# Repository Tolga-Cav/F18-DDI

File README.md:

# F18-DDI
Standalone F18 DDI with a screen to serve as general purpose second display for DCS

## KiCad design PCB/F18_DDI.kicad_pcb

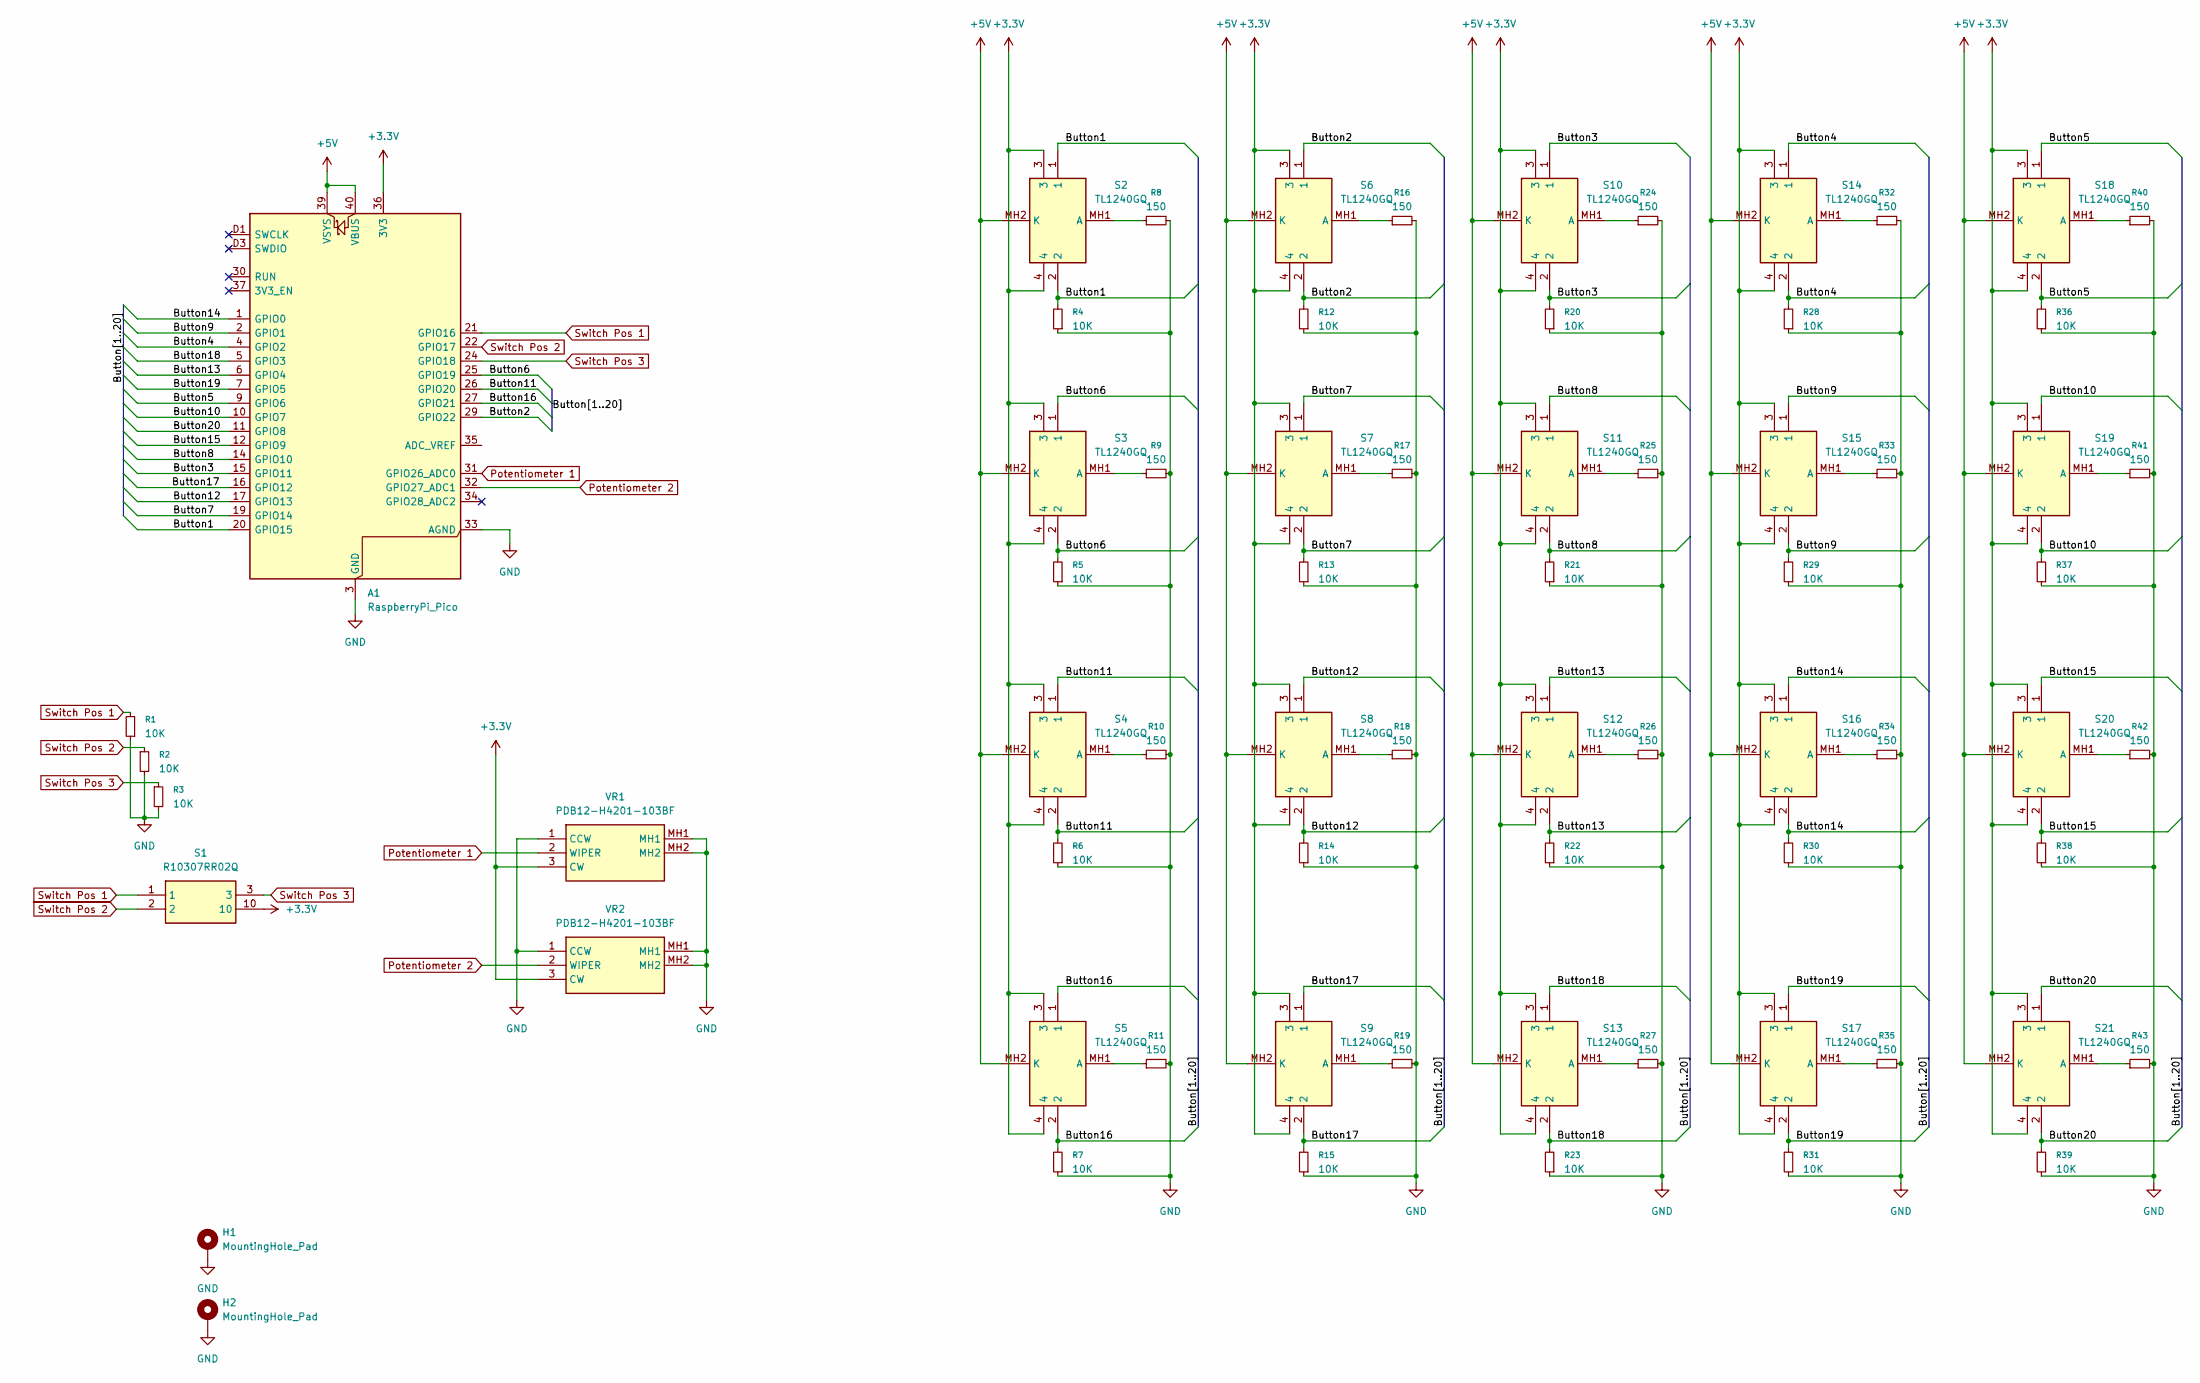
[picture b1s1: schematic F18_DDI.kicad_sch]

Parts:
A1: RaspberryPi_Pico; RaspberryPi_Pico_Common_Unspecified
H1, H2: MountingHole_Pad; MountingHole_3.2mm_M3_DIN965_Pad
R1, R2, R3, R4, R5, R6, R7, R12, R13, R14, R15, R20, R21, R22, R23, R28, R29, R30, R31, R36, R37, R38, R39: 10K; R_1206_3216Metric_Pad1.30x1.75mm_HandSolder
R8, R9, R10, R11, R16, R17, R18, R19, R24, R25, R26, R27, R32, R33, R34, R35, R40, R41, R42, R43: 150; R_1206_3216Metric_Pad1.30x1.75mm_HandSolder
S1: R10307RR02Q; R10305RN02Q; Mouser Part Number 611-R10307RR02Q
S2, S3, S4, S5, S6, S7, S8, S9, S10, S11, S12, S13, S14, S15, S16, S17, S18, S19, S20, S21: TL1240GQ; Mouser Part Number 612-TL1240GQ
VR1, VR2: PDB12-H4201-103BF; PDB12H4201103BF; Mouser Part Number 652-PDB12-H4201103BF

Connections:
+3.3V: A1.36 (3V3), S1.10, S2.3, S2.4, S3.3, S3.4, S4.3, S4.4, S5.3, S5.4, S6.3, S6.4, S7.3, S7.4, S8.3, S8.4, S9.3, S9.4, S10.3, S10.4, S11.3, S11.4, S12.3, S12.4, S13.3, S13.4, S14.3, S14.4, S15.3, S15.4, S16.3, S16.4, S17.3, S17.4, S18.3, S18.4, S19.3, S19.4, S20.3, S20.4, S21.3, S21.4, VR1.3 (CW), VR2.3 (CW)
+5V: A1.39 (VSYS), A1.40 (VBUS), S2.MH2 (K), S3.MH2 (K), S4.MH2 (K), S5.MH2 (K), S6.MH2 (K), S7.MH2 (K), S8.MH2 (K), S9.MH2 (K), S10.MH2 (K), S11.MH2 (K), S12.MH2 (K), S13.MH2 (K), S14.MH2 (K), S15.MH2 (K), S16.MH2 (K), S17.MH2 (K), S18.MH2 (K), S19.MH2 (K), S20.MH2 (K), S21.MH2 (K)
/Button1: A1.20 (GPIO15), R4.2, S2.1, S2.2
/Button2: A1.29 (GPIO22), R12.2, S6.1, S6.2
/Button3: A1.15 (GPIO11), R20.2, S10.1, S10.2
/Button4: A1.4 (GPIO2), R28.2, S14.1, S14.2
/Button5: A1.9 (GPIO6), R36.2, S18.1, S18.2
/Button6: A1.25 (GPIO19), R5.2, S3.1, S3.2
/Button7: A1.19 (GPIO14), R13.2, S7.1, S7.2
/Button8: A1.14 (GPIO10), R21.2, S11.1, S11.2
/Button9: A1.2 (GPIO1), R29.2, S15.1, S15.2
/Button10: A1.10 (GPIO7), R37.2, S19.1, S19.2
/Button11: A1.26 (GPIO20), R6.2, S4.1, S4.2
/Button12: A1.17 (GPIO13), R14.2, S8.1, S8.2
/Button13: A1.6 (GPIO4), R22.2, S12.1, S12.2
/Button14: A1.1 (GPIO0), R30.2, S16.1, S16.2
/Button15: A1.12 (GPIO9), R38.2, S20.1, S20.2
/Button16: A1.27 (GPIO21), R7.2, S5.1, S5.2
/Button17: A1.16 (GPIO12), R15.2, S9.1, S9.2
/Button18: A1.5 (GPIO3), R23.2, S13.1, S13.2
/Button19: A1.7 (GPIO5), R31.2, S17.1, S17.2
/Button20: A1.11 (GPIO8), R39.2, S21.1, S21.2
GND: A1.3 (GND), A1.8 (GND), A1.13 (GND), A1.18 (GND), A1.23 (GND), A1.28 (GND), A1.33 (AGND), A1.38 (GND), A1.D2 (GND), H1.1, H2.1, R1.1, R2.2, R3.2, R4.1, R5.1, R6.1, R7.1, R8.2, R9.2, R10.2, R11.2, R12.1, R13.1, R14.1, R15.1, R16.2, R17.2, R18.2, R19.2, R20.1, R21.1, R22.1, R23.1, R24.2, R25.2, R26.2, R27.2, R28.1, R29.1, R30.1, R31.1, R32.2, R33.2, R34.2, R35.2, R36.1, R37.1, R38.1, R39.1, R40.2, R41.2, R42.2, R43.2, VR1.1 (CCW), VR1.MH1, VR1.MH2, VR2.1 (CCW), VR2.MH1, VR2.MH2
unnamed: R8.1, S2.MH1 (A)
unnamed: R9.1, S3.MH1 (A)
unnamed: R10.1, S4.MH1 (A)
unnamed: R11.1, S5.MH1 (A)
unnamed: R16.1, S6.MH1 (A)
unnamed: R17.1, S7.MH1 (A)
unnamed: R18.1, S8.MH1 (A)
unnamed: R19.1, S9.MH1 (A)
unnamed: R24.1, S10.MH1 (A)
unnamed: R25.1, S11.MH1 (A)
unnamed: R26.1, S12.MH1 (A)
unnamed: R27.1, S13.MH1 (A)
unnamed: R32.1, S14.MH1 (A)
unnamed: R33.1, S15.MH1 (A)
unnamed: R34.1, S16.MH1 (A)
unnamed: R35.1, S17.MH1 (A)
unnamed: R40.1, S18.MH1 (A)
unnamed: R41.1, S19.MH1 (A)
unnamed: R42.1, S20.MH1 (A)
unnamed: R43.1, S21.MH1 (A)
Potentiometer 1: A1.31 (GPIO26_ADC0), VR1.2 (WIPER)
Potentiometer 2: A1.32 (GPIO27_ADC1), VR2.2 (WIPER)
Switch Pos 1: A1.21 (GPIO16), R1.2, S1.1
Switch Pos 2: A1.22 (GPIO17), R2.1, S1.2
Switch Pos 3: A1.24 (GPIO18), R3.1, S1.3

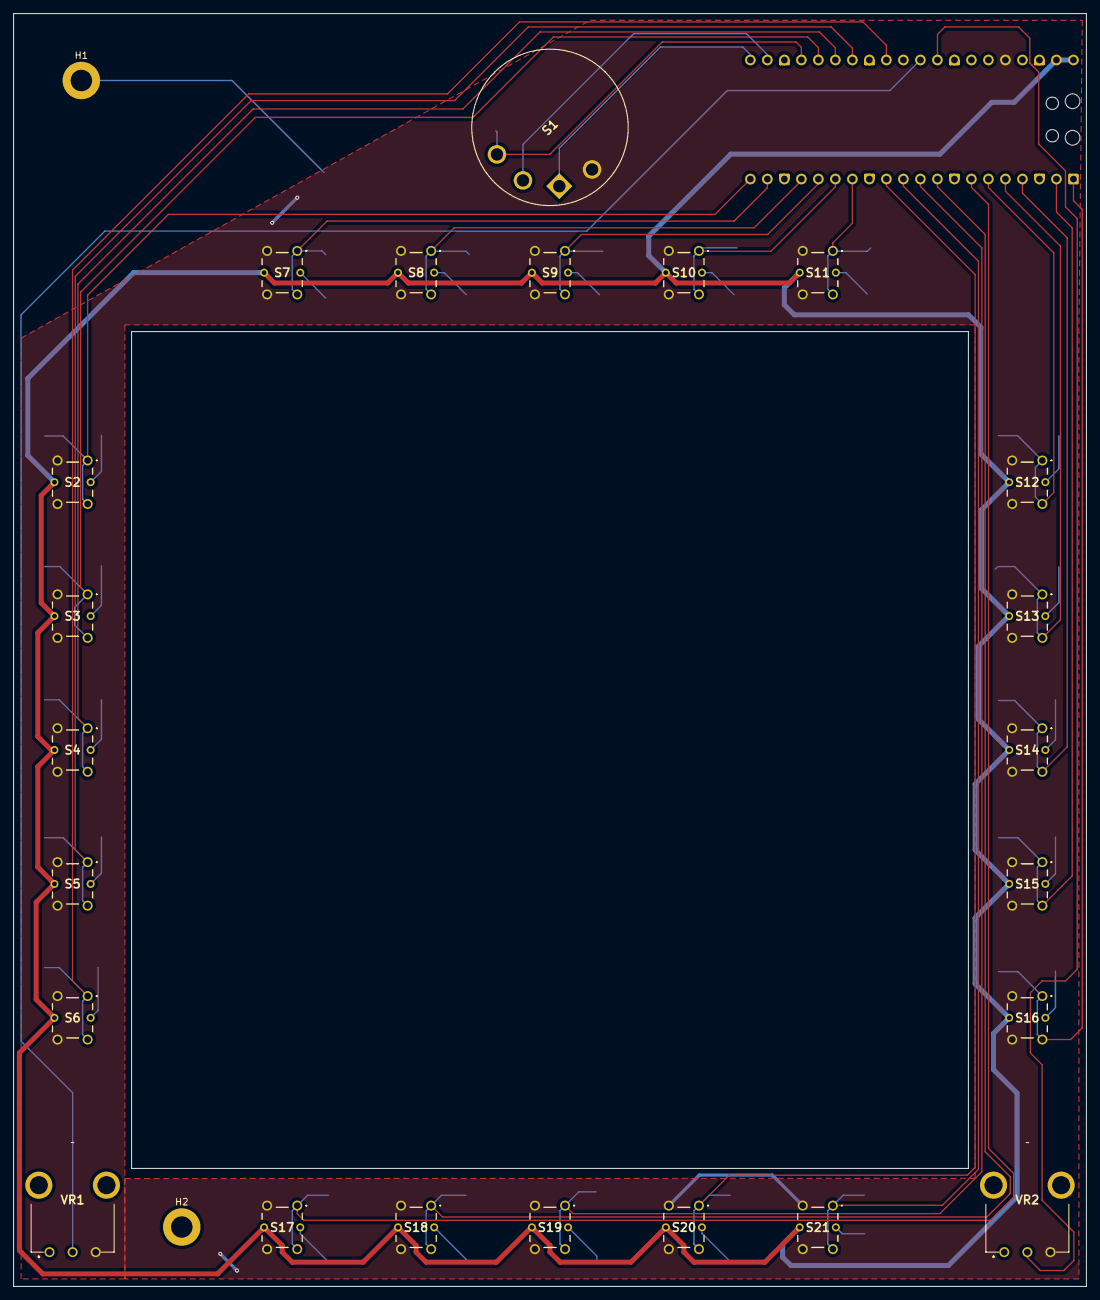
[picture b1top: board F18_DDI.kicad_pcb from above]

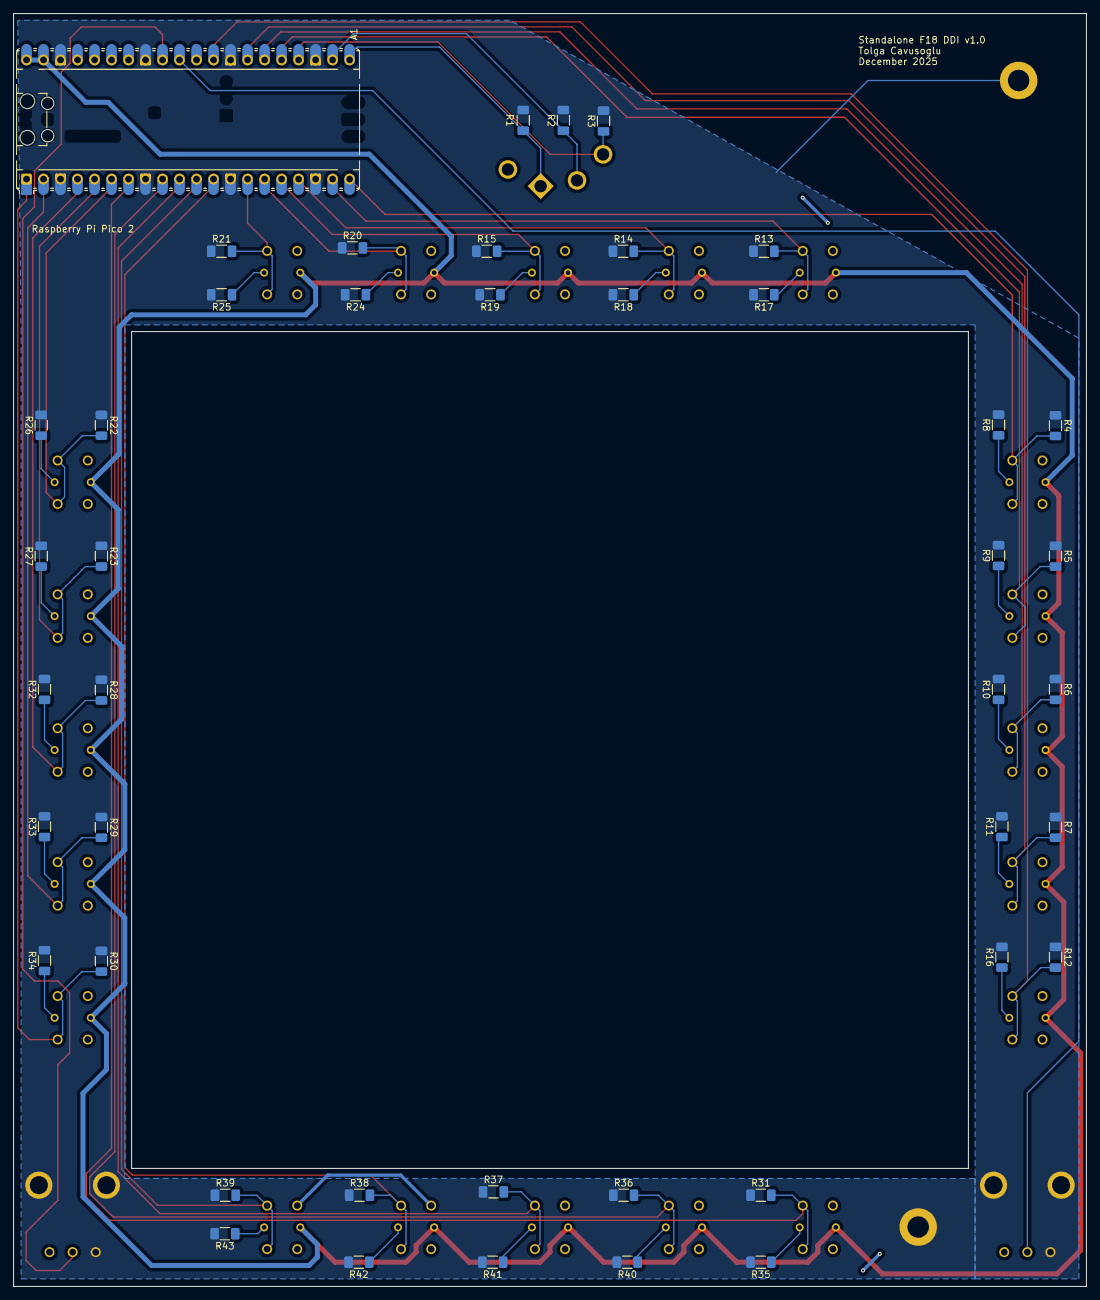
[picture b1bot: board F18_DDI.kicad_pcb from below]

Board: 2 copper layers, 160.2 x 190.1 mm, 69 parts (44 on the bottom side), 48 nets.

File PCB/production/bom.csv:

Designator,Footprint,Quantity,Value,LCSC Part #
A1,RaspberryPi_Pico_Common_Unspecified,1,RaspberryPi_Pico,
"R1, R12, R13, R14, R15, R2, R20, R21, R22, R23, R28, R29, R3, R30, R31, R36, R37, R38, R39, R4, R5, R6, R7",1206,23,10K,
"R10, R11, R16, R17, R18, R19, R24, R25, R26, R27, R32, R33, R34, R35, R40, R41, R42, R43, R8, R9",1206,20,150,
S1,R10305RN02Q,1,R10307RR02Q,
"S10, S11, S12, S13, S14, S15, S16, S17, S18, S19, S2, S20, S21, S3, S4, S5, S6, S7, S8, S9",TL1240GQ,20,TL1240GQ,
"VR1, VR2",PDB12H4201103BF,2,PDB12-H4201-103BF,

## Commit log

2025-11-23 Initial Commit
    Set up projects and begin schematic
2025-11-23 Set up workspace
    Set up inventor and kicad projects and begin schematic
2025-11-24 Finish electrical schematic
2025-12-16 preliminary pcb layout
2025-12-17 Finalize PCB
2025-12-18 Update silkscreen
2025-12-21 Add manufacturing files
